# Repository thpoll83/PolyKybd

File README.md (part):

# PolyKybd Split72

Official hardware repository of the PolyKybd Split72 keyboard. If you are looking for the kit, jump immediately to https://www.crowdsupply.com/polykybd/polykybd for registration.

The instructions here are still in a very early stage. There is also a build video available: https://www.youtube.com/watch?v=K5RpbYzx7gw

You can find the matching QMK firmware here: [https://github.com/thpoll83/qmk_firmware/tree/PolyKybd](https://github.com/thpoll83/qmk_firmware/tree/PolyKybd)

## Cloning this repository

This repo is big — around 800 MB of history. Most of that is the board files themselves: the
decorative silkscreen artwork is stored as vector polygons, which makes a single `.kicad_pcb`
around 50 MB, and there are several design generations in the history.

If you just want the current files, use a partial clone. Git then downloads file contents only
when you actually touch them, so a fresh checkout takes seconds instead of many minutes:

```
git clone --filter=blob:none https://github.com/thpoll83/PolyKybd.git
```

The full history is still there and everything works normally — `git log`, `git checkout`, opening
the boards in KiCad. Older revisions of large files are simply fetched on demand. If you want a
plain full clone instead, just leave the `--filter` off.

The PCB projects are the following (**KiCad 9** — the schematics were migrated to the version 9
file format, so KiCad 8 and earlier can no longer open them):

[poly_kybd/poly_kybd_split72_right.kicad_pro](poly_kybd/poly_kybd_split72_right.kicad_pro)
[poly_kybd/poly_kybd_split72_left.kicad_pro](poly_kybd/poly_kybd_split72_left.kicad_pro)

(please just use the projects linked above and ignore any older/backup projects in the folder)

Here are the corresponding schematics for reference (left and right):

You can inspect all individual schematic sheets (with descriptions) here: [Schematic sheets](schematics.md).

The keyboard plates are also KiCad projects, still in an older file format but they open fine in
KiCad 9 (I used 1.2mm aluminum PCBs):

[poly_kybd/poly_kybd_split72_plate_right.kicad_pro](poly_kybd/poly_kybd_split72_plate_right.kicad_pro)
[poly_kybd/poly_kybd_split72_plate_left.kicad_pro](poly_kybd/poly_kybd_split72_plate_left.kicad_pro)

## How to Build

I recommend waiting for the kit that contains all parts and the assembled PCBs. Here a little preview, how that looks like:

The kits are not yet ready, but you can sign up here and get notified as soon as these are available: [https://www.crowdsupply.com/polykybd/polykybd](https://www.crowdsupply.com/polykybd/polykybd)

At the moment, please consider these instructions as experimental. If you want to go ahead with the full experience and build everything from scratch right now: Give it a try and let me know how it worked out!

Independent of your choice, here are the parts you need before putting everything together:

### Prepare Required Parts

* Case (left/right) - You can either 3D print or get them CNCed (but then you should add some threads to the screw holes):
  [parts/export/case/case_polykybd_split72_left_r7.stl](parts/export/case/case_polykybd_split72_left_r7.stl)
  
  [parts/export/case/case_polykybd_split72_right_r7.stl](parts/export/case/case_polykybd_split72_right_r7.stl)
  
  In case the resin print has some deformations, it is best to use a hairdryer to slightly heat the case up and then put something heavy on the bottom to make it flat - it really works.
* Spacer to keep the right distance between plate and PCB (again, can be 3D printed):
  [parts/export/case/spacer.stl](parts/export/case/spacer.stl). If you fit the LED diffuser frame, print [parts/export/case/spacer_diffuser_frame.stl](parts/export/case/spacer_diffuser_frame.stl) instead. It is notched for the frame on both faces, so one part works on either half.
  
* Assembled 4 layers PCB 1.6mm (left/right)
  The latest gerber files with BOM and pick/place file can be found in [poly_kybd/Gerber](poly_kybd/Gerber) I made some final adjusts on the latest version, which I did not yet order (I will let you know as soon as I did).
  [poly_kybd/Gerber/PCB/left-side-v3.2/PolyKybd_Split72_L_3.2.zip](poly_kybd/Gerber/PCB/left-side-v3.2/PolyKybd_Split72_L_3.2.zip)
  [poly_kybd/Gerber/PCB/right-side-v3.2/PolyKybd_Split72_R_3.2.zip](poly_kybd/Gerber/PCB/right-side-v3.2/PolyKybd_Split72_R_3.2.zip)

  My recommendation is to let assemble the PCBs as there are a lot of parts with tiny footprints like the RP2040, the 72 FPC sockets and some more...
  If your PCB fab has an option to verify the parts orientation, please make use of it. I did that as well and never bothered correcting them (since the 'upright' orientation of the part from KiCad and your PCB fab might differ).

  ###### Note:

  In case you make modifications to the PCB in KiCad and export everything you might need to change the hot swap sockets side to the back. The hot swap socket in KiCad is part of the key switch and for some reason I couldn't yet convince KiCad that the manufacturing side is the back...
* Aluminum plates (left/right =) - Can be ordered from PCB manufactures as a 1.2mm aluminum PCB
  [poly_kybd/Gerber/Plate/gerber-left-side-v3-17.11.2023.zip](poly_kybd/Gerber/Plate/gerber-left-side-v3-17.11.2023.zip)
  [poly_kybd/Gerber/Plate/gerber-right-side-v3-17.11.2023.zip](poly_kybd/Gerber/Plate/gerber-right-side-v3-17.11.2023.zip)
* Displays

  - 72 pieces 0.42 inch displays

    - Either you take the 0.42 inch displays from the kit which has the matching length and pin number (maybe I can make them available as single parts as well - see picture above, on the left).
    - Or make them yourself the manual way, by extending a compatible 0.42 inch OLED with a short FPC cable and soldering the two together. See [Making the displays manually](making_the_displays_manually.md) for suppliers and the full soldering instructions.
  - (Optional) 2 pieces 0.96 inch status displays (FPW096W001Z0) or pin compatible (see below), the flex cable length should be about 40mm or you extend it on your own. You can contact this supplier: [FET](https://fetoled.en.alibaba.com/search/product), they have these displays even they are not listed in their online catalogue.

    | PIN   | SIGNAL    | PIN   | SIGNAL |
    | ----- | --------- | ----- | ------ |
    | 1,30  | N/C (GND) | 14    | RES#   |
    | 2,3   | C2P,C2N   | 15    | D/C#   |
    | 4,5   | C1P,C1N   | 16    | R/W#   |
    | 6     | VDDB/VBAT | 17    | E/RD#  |
    | 7     | N/C       | 18~25 | D0~D7  |
    | 8     | VSS       | 26    | IREF   |
    | 9     | VDD       | 27    | VCOMH  |
    | 10~12 | BS0~BS2   | 28    | VCC    |
    | 13    | CS#       | 29    | VLSS   |

    If you don't need the status displays, you can close the display cut-out with the dummy holder: [Dummy Display Holder](parts/export/display_holder/display_holder_dummy_r1.stl)

* MX Compatible key switches (3 or 5 pins) - 72 pieces. From my blog post ( [https://ko-fi.com/post/More-Key-Switch-Testing-While-Waiting-For-The-Asse-B0B8HX1HW](https://ko-fi.com/post/More-Key-Switch-Testing-While-Waiting-For-The-Asse-B0B8HX1HW) ), you can find out, that there are 2 categories of compatible key switches. The ones that work out of the box and the ones that need a little modification. Basically all switches that have an LED slit that is at least 7.5mm wide work. I tested quite some switches and here is the list of tested switches that will work for sure without modification:

  | SWITCH                            | TYPE            | MISC  |
  | --------------------------------- | --------------- | ----- |
  | Aflion Tropical Waters            | Linear          | 68g   |
  | Ashkeebs Alexandrite              | Linear          | 58g   |
  | Blue Dusk Panda                   | Linear          | 62g   |
  | BSUN x Unikeys Udon               | Linear          | 48g   |
  | CK x Haimu Pastel Lemon           | Linear          | 63.5g |
  | Ck x Haimu Pastel Thistle         | Tactile         | 63.5g |
  | Gateron KS-9 (Pro) Blue           | Clicky          | 60g   |
  | Gateron KS-9 (Pro) Brown          | Tactile         | 55g   |
  | Gateron KS-9 (Pro) Green          | Clicky          | 80g   |
  | Gateron KS-9 (Pro) Red            | Linear          | 45g   |
  | Gateron KS-9 (Pro) Yellow         | Linear          | 50g   |
  | Geon Black                        | Tactile         | 60g   |
  | Geon Clear                        | Linear          | 60g   |
  | Geon Yellow                       | Linear          | 63.5g |
  | Glorious Panda                    | Tactile         | 67g   |
  | GOJU Works x Tecsee Safety Switch | Linear          | 65g   |
  | HMX Cthulhu                       | Linear          | 45-50g|
  | HMX Emo                           | Linear          | 40g   |
  | HMX Hazelnut V2                   | Linear          | 43g   |
  | HMX K01 Light                     | Tactile         | 45g   |
  | HMX Lotus                         | Linear          | 62.5g |
  | HMX Su Color Pink                 | Linear          | 45g   |
  | HMX x Sillyworks Sonja            | Linear          | 45g   |
  | HMX x Unikeys Purple Dawn         | Linear          | 55g   |
  | Kailh Novel Keys Cream Switch     | Linear          | 55g   |
  | Kailh Purple Potato               | Tactile         | 63.5g |
  | Kailh x Domikey Knight Saber      | Tactile         | 42g   |
  | Keygeek M3                        | Linear          | 48g   |
  | LCET Grace                        | Linear          | 50g   |
  | LCET Joker                        | Tactile         | 58g   |
  | LCET Pink Queen                   | Tactile         | 58g   |
  | LCET Sprout                       | Linear          | 50g   |
  | MMD Holy Panda V3                 | Tactile         | 45g   |
  | Outemu (Dustproof) Black          | Linear          | 65g   |
  | Outemu (Dustproof) Blue           | Clicky          | 65g   |
  | Outemu (Dustproof) Brown          | Tactile         | 50g   |
  | Outemu (Dustproof) Red            | Linear          | 46g   |
  | Outemu Crystal Clear              | Linear          | 45g   |
  | Outemu Dust-proof Silver          | Linear          | 45g   |
  | Outemu Lemon                      | Silent Tactile  | 35g   |
  | Outemu Panda                      | Tactile         | 50g   |
  | Outemu Peach                      | Linear          | 40g   |
  | Outemu Purple                     | Tactile         | 45g   |
  | Outemu Ocean                      | Linear          | 35g   |
  | Outemu Teal                       | Clicky          | 70g   |
  | Owlab Neon                        | Linear          | 62g   |
  | Tecsee Medium (low profile)       | Linear & Tactile| 50g   |

  Be aware that there are different batches of Gateron KS-9 (with and without 'Pro') switches. Despite the exact same name, they might need the following surgery (better ask before buy).
  So, some switches have an LED slit, but with a little plastic bar in the middle:

  You can simply cut it away with a knife:

  It is not a big deal, just consider it. Here is a list of switches that I successfully tested after this little modification:

  | SWITCH                           | TYPE           | MISC |
  | -------------------------------- | -------------- | ---- |
  | Gateron KS-9 (Pro 2.0) Red       | Linear         | 45g  |
  | Gateron KS-9 (Pro 2.0) White     | Linear         | 35g  |
  | Geon HG [Haimu x Geon] Black     | Linear         | 65g  |
  | Geon HG [Haimu x Geon] White     | Tactile        | 65g  |
  | Geon HG [Haimu x Geon] Red       | Silent Linear  | 65g  |
  | Geon HG [Haimu x Geon] Yellow    | Silent Tactile | 65g  |
  | Kailh BOX V2 Red Switch          | Linear         | 40g  |
  | Kailh Box Cream                  | Linear         | 45g  |
  | Kailh Pro Purple                 | Tactile        | 50g  |
  | Kailh Pro Burgundy               | Linear         | 50g  |
  | Kailh Pro Light Green            | Clicky         | 50g  |
  | Kailh Pro Plum                   | Tactile        | 70g  |
  | Kailh Speed Gold                 | Clicky         | 50g  |
  | Kailh Speed Silver               | Linear         | 50g  |
  | Kailh Speed Bronze               | Clicky         | 50g  |
  | Kailh Speed Copper               | Tactile        | 40g  |
  | Kailh Speed Burnt Orange         | Linear/Tactile | 70g  |
  | Kailh Speed Pro Heavy Army Green | Clicky         | 70g  |
  | Kailh Speed Pro Heavy Yellow     | Linear         | 70g  |
  | Kailh Black                      | Linear         | 60g  |
  | Kailh RGB Red                    | Linear         | 45g  |
  | Kailh RGB Black                  | Linear         | 60g  |
  | Kailh RGB Blue                   | Clicky         | 50g  |
  | Kailh RGB Brown                  | Tactile        | 50g  |

  There are many more switches that will work as long as they have a 7.5mm wide LED slit. Let me know in case you successfully tried another switch, then I can update the list.

* Key Stems - 72 pieces, can be 3D printed (I highly recommend using an SLA printer). There are 3 different profiles available here. You can also modify the source file an make your own profile. If you take the STLs, make sure to always grab the latest version.

  Every plate is in [parts/export/keycap_stem/](parts/export/keycap_stem), named
  `keycap_stem_revAlpha_<width>_<profile>_10p.stl` — where *width* is `1U` or
  **`1U25`** (not `1.25U`) and *profile* is one of `R1`–`R5`, `S1`, `S`, `S5`, e.g.
  `keycap_stem_revAlpha_1U25_R1_10p.stl`. Ten pieces per plate, so divide the
  counts below by ten (rounding up) to know how many of each to print.

  Every piece carries its **profile and revision engraved on the top face**
  (`R5 α`, `S1 α`, …), matching the profile token in the filename — so a printed
  stem can always be traced back to the plate that made it, and a mixed handful
  can be sorted back out.

  - Flat 
    One stem for every row: the `R3` plates (14 pieces 1.25U and 58 pieces 1U).
  - Stepped 
    Rows tilted rather than curved. This works best if the keyboard is inclined by 5 degrees or more, and comes in two variations:
    - *sculpted* (pictured) — `S1` on the front row, `S5` on the back row, `S` on the three rows between: 4x 1.25U S1, 10x 1U S1, 8x 1.25U S, 36x 1U S, 2x 1.25U S5, 12x 1U S5.
    - *uniform* 
      just the `S` plates everywhere (14 pieces 1.25U and 58 pieces 1U) — a flatter feel that is simpler to print, since it is a single plate design.
  - Curved 
    Here you will need `R1` to `R5`: 4x 1.25U R1, 10x 1U R1, 4x 1.25U R2, 12x 1U R2, 2x 1.25U R3, 12x 1U R3, 2x 1.25U R4, 12x 1U R4, 2x 1.25U R5, 12x 1U R5.

  To change a profile or add your own, edit the shared
  [parts/keycap_stem/keycap_stem.scad](parts/keycap_stem/keycap_stem.scad) or add a
  file to [parts/keycap_stem/variants/](parts/keycap_stem/variants), then run
  `parts/keycap_stem/build_stems.sh` — see [parts/README.md](parts/README.md).
* Status display holder (or cover/dummy in case no status display is used), can be 3D printed.
  [parts/export/display_holder/display_holder_r1.stl](parts/export/display_holder/display_holder_r1.stl) / [parts/export/display_holder/display_holder_dummy_r1.stl](parts/export/display_holder/display_holder_dummy_r1.stl)
* LED diffuser frame (optional, recommended) - one part per half. Each key's LED shines through a half-round hole in the plate, and without a diffuser it shows as a bright point. The frame holds all 36 diffusers of one half at their plate positions, connected by a web under the plate. Print it in resin (SLA): it is thin, and the web is close to the 0.8mm minimum wall a print service accepts.
  [parts/export/diffuser/diffuser_frame_left.stl](parts/export/diffuser/diffuser_frame_left.stl) / [parts/export/diffuser/diffuser_frame_right.stl](parts/export/diffuser/diffuser_frame_right.stl) (the `_4x` files stack four copies on top of each other, joined by a sprue so that a print service counts one part; the slicer still needs supports between the copies, and you cut the pins off before fitting)
  With the frame you need the other spacer, `spacer_diffuser_frame.stl` (see Spacer above), because the plain spacer has no room for the web.
* Transparent keycap covers - 72 pieces (from relegendable keycaps [like these](https://de.aliexpress.com/item/1005002996832179.html?spm=a2g0o.order_list.order_list_main.111.49985c5f1EyPsm&gatewayAdapt=glo2deu)), 58x 1U and 14x 1.25U. Various sources sell them on Alibaba, AliExpress, Amazon & Co.
* Optional rotary encoder ([EVQWGD001](https://de.aliexpress.com/i/32990950196.html?gatewayAdapt=gloMsite2deuPcglo2deu) or [Alps EC11 Encoder](https://www.mouser.at/c/electromechanical/encoders/?m=Alps%20Alpine&series=EC11)), [pimoroni trackball](https://mou.sr/3rmFiAO) or [23mm cirque trackpad](https://www.mouser.at/ProductDetail/Cirque/TM023023-2024-002?qs=wd5RIQLrsJhgKZTW4CXgsA%3D%3D&countryCode=DE&currencyCode=EUR) (and a 12 pin FPC cable with pins on the same side, about 50mm to 70mm). For the trackpad you will need another 3D printed holder, either a high one or a low one: 
  [parts/export/cirque_insert/cirque23_slim_insert_r8.stl](parts/export/cirque_insert/cirque23_slim_insert_r8.stl)
  [parts/export/cirque_insert/cirque23_insert_high_r1.stl](parts/export/cirque_insert/cirque23_insert_high_r1.stl)
  If you are not happy with the existing STLs, you can also modify the source file [parts/cirque_insert/cirque23_insert.scad](parts/cirque_insert/cirque23_insert.scad) or [parts/cirque_insert/cirque23_slim_insert.scad](parts/cirque_insert/cirque23_slim_insert.scad). There is also an experimental version for the 35mm cirque track pad: [parts/cirque_insert/cirque35_insert.scad](parts/cirque_insert/cirque35_insert.scad).
* Optional ambient-light + proximity sensor (**highly recommended**) - a [Pimoroni LTR-559 Light & Proximity Sensor breakout](https://shop.pimoroni.com/products/ltr-559-light-proximity-sensor-breakout) plus a matching 5-pin 2.54mm pin header. The Split72 PCB has a dedicated header footprint for it (labelled `3-6V / SDA / SCL / INT / GND`), sharing the Cirque I2C bus - no extra wiring. With the sensor fitted, the firmware automatically drives keycap brightness from the measured light level and wakes the displays when your hand approaches. It is entirely optional (the firmware is a clean no-op when no sensor is present) and side-agnostic (works on whichever half you solder it to). **You must fit it as the very first assembly step** - see the note in [Put Everything Together](#put-everything-together) below, because it does *not* fit through the plate hole and cannot be added later without an almost complete disassembly. 
  ***Note:*** each half has a **single** expansion slot that takes exactly **one** of these optional add-ons - a rotary encoder, a pointing device (trackball/trackpad), *or* the light sensor. So on a given half the sensor is mutually exclusive with the encoder and the pointing device: fitting the sensor means that half has no encoder/trackpad. (You can still put the sensor on one half and a pointing device or encoder on the other.)
* Short USB-C to USB-C cable to connect the two sides (maybe around 50cm).
* USB-C to USB-A/USB-C to connect to your computer.
  ***Note:*** I had a USB-C to USB-A cable and was sitting in front of a laptop with only USB-C ports. Without a USB-C to USB-C cable at hand, I used an USB-A to USB-C adapter. It turned out this USB-C to USB-A cable + USB-A to USB-C adapter construction was only working then the adapter was connected to the laptop. - better use a USB-C to USB-C right away.
* 8 M3x10 hex screws with rounded heads and for the current case version (r4 and later, e.g. r7), you also need 8 M3 hex nuts.

### Put Everything Together

Here is my recommended order:

0. **(Optional but highly recommended) Solder the LTR-559 light + proximity sensor - do this FIRST!**
   ⚠️ The sensor board does **not** fit through the hole in the aluminum plate, so it has to be soldered on **before** the plate goes on. If you add it later you will have to almost completely disassemble the keyboard again. So if there is any chance you want it, fit it now - it is optional in firmware and costs you nothing if you later decide not to use it.
   ⚠️ Each half has a **single** expansion slot shared by the sensor, the rotary encoder and a pointing device (trackball/trackpad) - only **one** of the three fits per half. So fitting the sensor means no encoder or trackpad on that half (you can still fit one of those on the other half). Decide before you start soldering.

   The Split72 PCB has a labelled 5-pin footprint for the sensor (`3-6V / SDA / SCL / INT / GND`). Solder the sensor exactly like this:
   1. Solder the 5-pin header into the PCB footprint.
   2. The plastic spacer strip of the header now has to come off - it holds the sensor board too high to clear the plate. I simply pushed it all the way down/off the pins:
      
   3. It is still too thick, so instead of the plastic spacer use a piece of paper folded twice (roughly 1-2mm) as a temporary shim to set the sensor at a nice low height while you solder the board onto the header pins:
      
   4. After soldering, pull the paper back out. The sensor now sits low and flat, just above the PCB:
      
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
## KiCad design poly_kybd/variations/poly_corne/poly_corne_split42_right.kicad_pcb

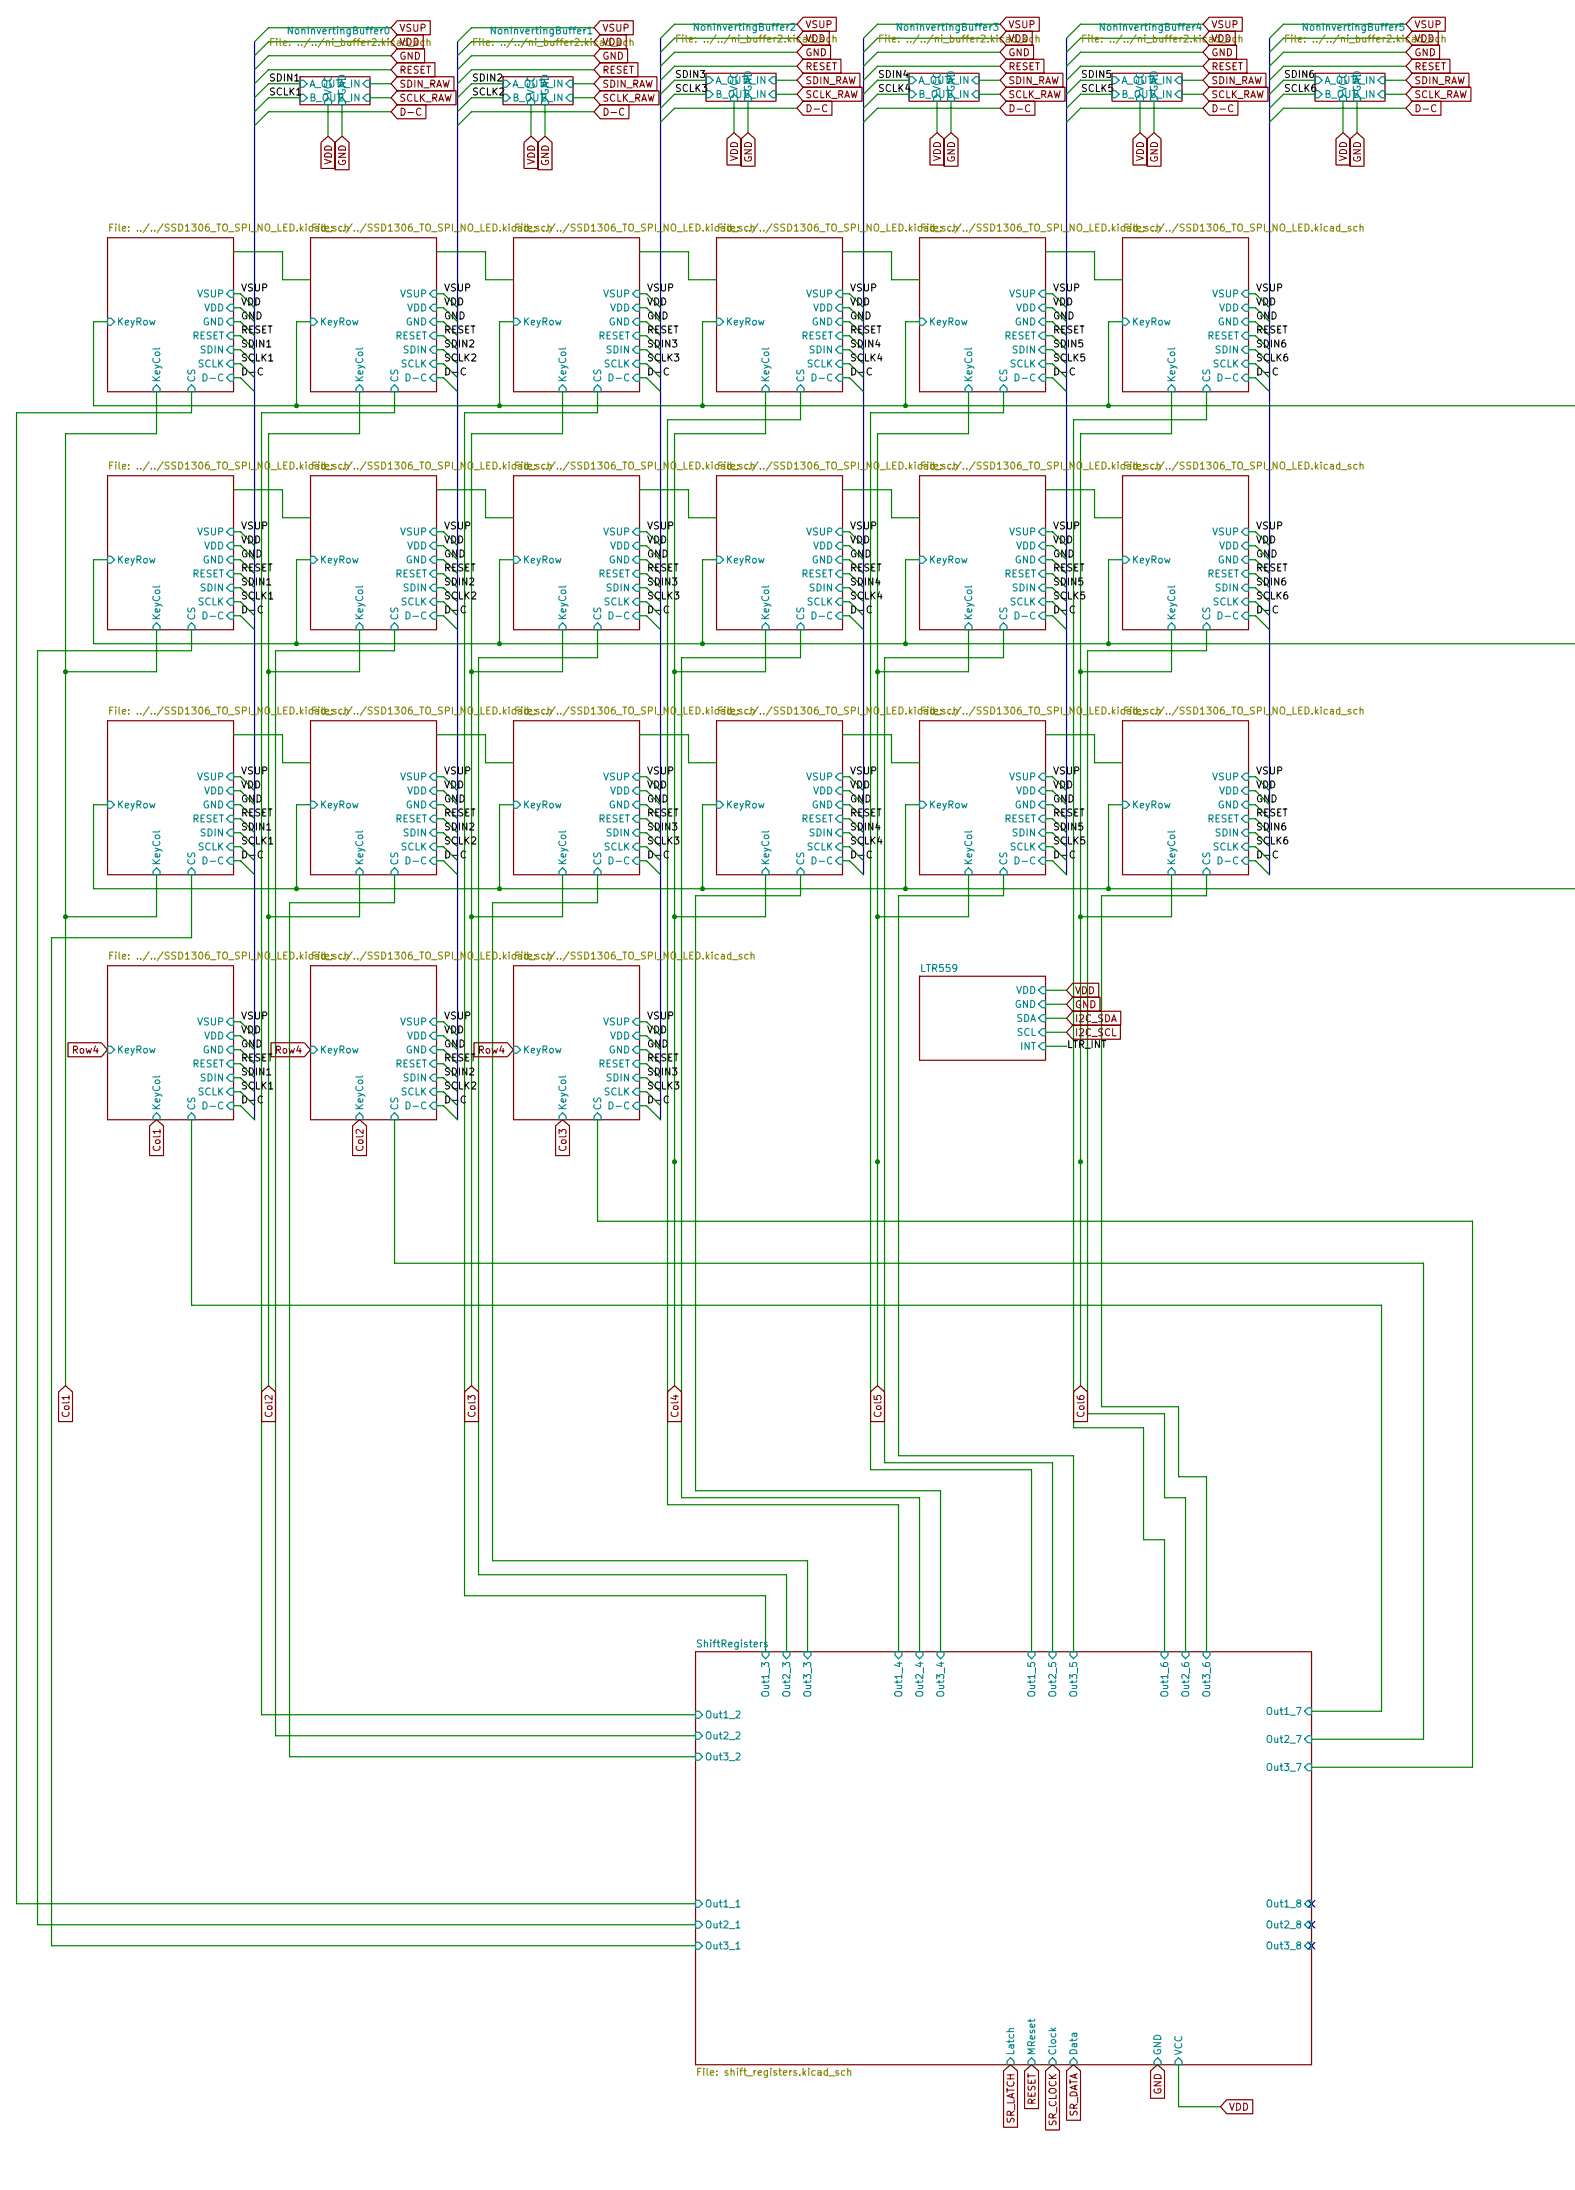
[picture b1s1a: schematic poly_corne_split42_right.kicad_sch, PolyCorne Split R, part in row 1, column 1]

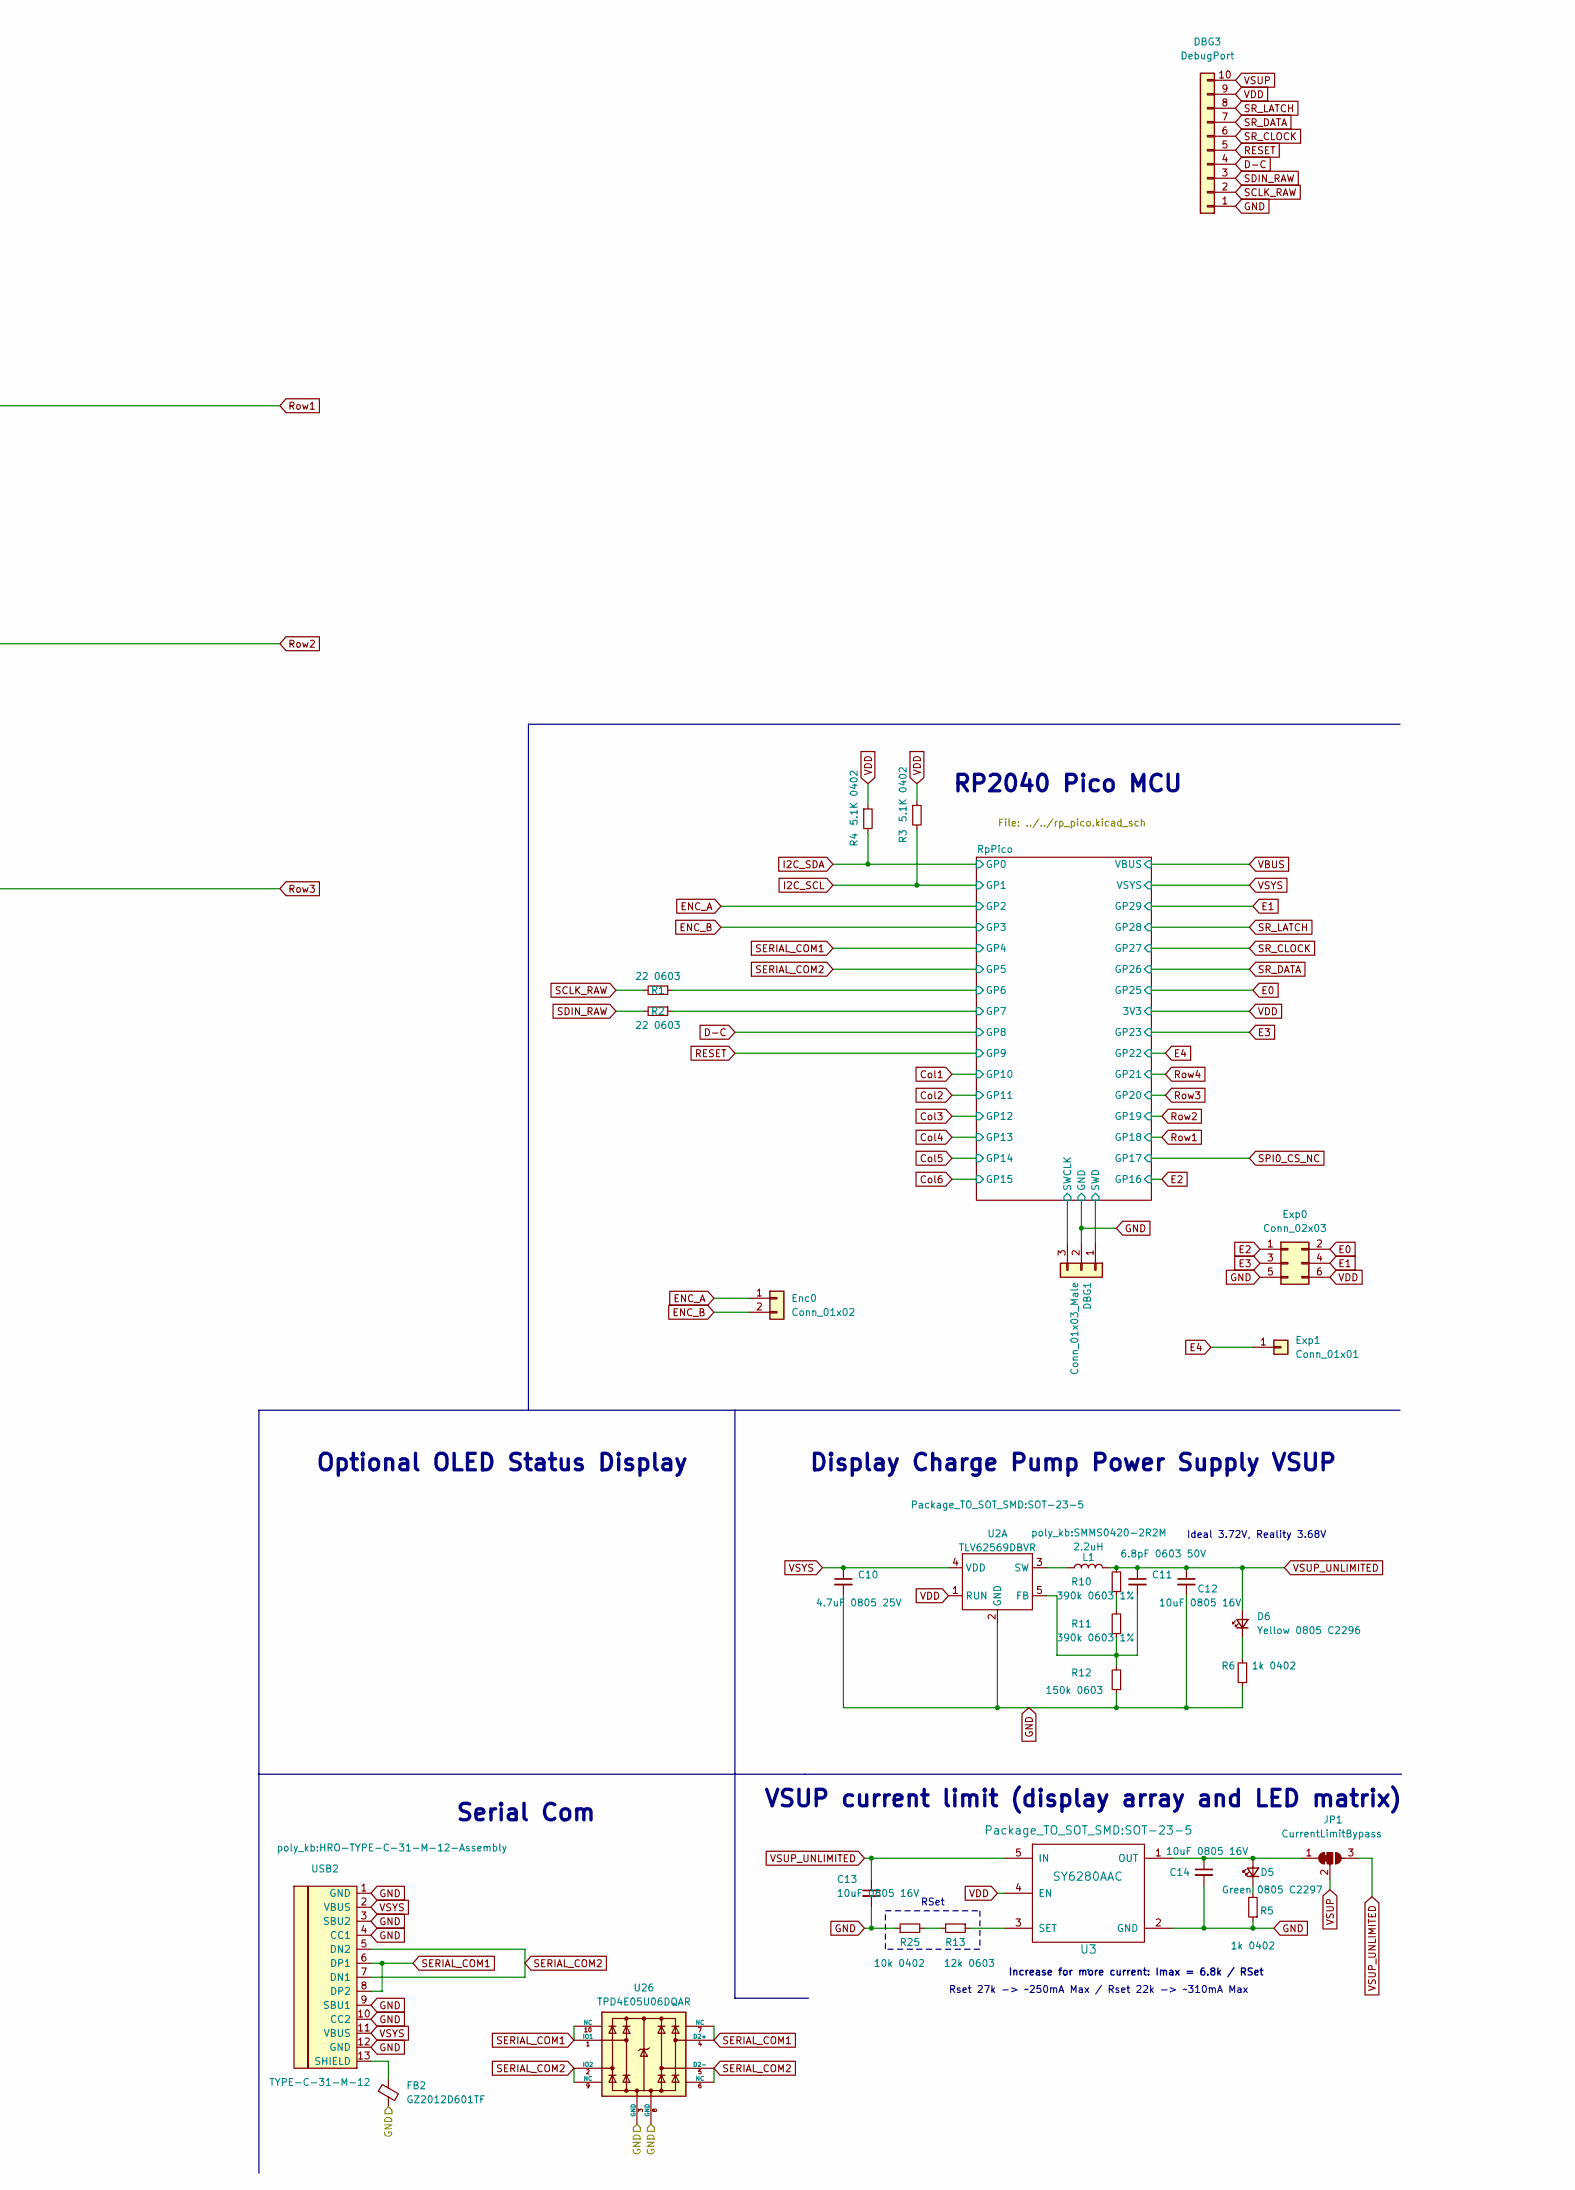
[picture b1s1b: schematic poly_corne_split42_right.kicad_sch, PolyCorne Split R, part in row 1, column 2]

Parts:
C10: 4.7uF 0805 25V; C_0805_2012Metric; MPN C1779; JLC C1779
C11: 6.8pF 0603 50V; C_0603_1608Metric; MPN CL10C6R8CB8NNNC; JLC C318672
C12, C13, C14: 10uF 0805 16V; C_0805_2012Metric; MPN C15850; JLC C15850
D5: Green 0805 C2297; LED_0805_2012Metric; MPN C2297; JLC C2297
D6: Yellow 0805 C2296; LED_0805_2012Metric; MPN C2296; JLC C2296
DBG1: Conn_01x03_Male; PinHeader_1x03_P2.54mm_Vertical; MPN DNP; JLC DNP
DBG3: DebugPort; PinHeader_1x10_P2.54mm_Vertical; MPN DNP; JLC DNP
Enc0: Conn_01x02; PinHeader_1x02_P2.54mm_Vertical; Part Number 1-0201FBV0T
Exp0: Conn_02x03; PinHeader_2x03_P1.27mm_Vertical; Part Number LL1009-2A, 2.54MM 2*3PIN HEADER,LENGTH=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
Exp1: Conn_01x01; PinHeader_1x01_P2.54mm_Vertical
FB2: GZ2012D601TF; L_0805_2012Metric; MPN C1017; JLC C1017
JP1: CurrentLimitBypass; SolderJumper-3_P1.3mm_Bridged12_RoundedPad1.0x1.5mm; MPN DNP; JLC DNP
L1: 2.2uH; SMMS0420-2R2M; MPN C133191; JLC C133191
R1, R2: 22 0603; R_0603_1608Metric; MPN C108405; JLC C108405
R3, R4: 5.1K 0402; R_0402_1005Metric; MPN C144745; JLC C144745
R5, R6: 1k 0402; R_0402_1005Metric; MPN CRCW04021K00FKED; JLC C71623
R10, R11: 390k 0603 1%; R_0603_1608Metric; MPN C137735; JLC C137735
R12: 150k 0603; R_0603_1608Metric; MPN C114660; JLC C114660
R13: 12k 0603; R_0603_1608Metric; MPN C114659; JLC C114659
R25: 10k 0402; R_0402_1005Metric; MPN C60490; JLC C60490
U2: TLV62569DBVR; SOT-23-5; MPN C141836; JLC C141836
U3: SY6280AAC; SOT-23-5; MPN C55136; JLC C55136
U26: TPD4E05U06DQAR; USON-10; MPN C2836386; JLC C2836386
USB2: TYPE-C-31-M-12; HRO-TYPE-C-31-M-12-Assembly; MPN C165948; JLC C165948

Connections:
/RpPico/GPIO6: R1.1; also elsewhere on the board
/RpPico/GPIO7: R2.1; also elsewhere on the board
/RpPico/SWCLK: DBG1.3; also elsewhere on the board
/RpPico/SWD: DBG1.1; also elsewhere on the board
D-C: DBG3.4; also elsewhere on the board
E0: Exp0.2 (+12V); also elsewhere on the board
E1: Exp0.4 (GND); also elsewhere on the board
E2: Exp0.1 (+12V); also elsewhere on the board
E3: Exp0.3 (GND); also elsewhere on the board
E4: Exp1.1; also elsewhere on the board
ENC_A: Enc0.1; also elsewhere on the board
ENC_B: Enc0.2; also elsewhere on the board
GND: C10.2, C12.2, C13.2, C14.2, DBG1.2, DBG3.1, Exp0.5 (GND), FB2.2, R5.1, R6.1, R12.1, R25.1, U2.2 (GND), U3.2 (GND), U26.3 (GND), U26.8 (GND), USB2.1 (GND), USB2.3 (SBU2), USB2.4 (CC1), USB2.9 (SBU1), USB2.10 (CC2), USB2.12 (GND); also elsewhere on the board
I2C_SCL: R3.2; also elsewhere on the board
I2C_SDA: R4.2; also elsewhere on the board
unnamed: C14.1, D5.2 (A), JP1.1 (A), U3.1 (OUT)
unnamed: D5.1 (K), R5.2
unnamed: D6.1 (K), R6.2
unnamed: R10.1, R11.2
unnamed: R13.2, R25.2
unnamed: C11.2, R11.1, R12.2, U2.5 (FB)
unnamed: L1.1, U2.3 (SW)
unnamed: R13.1, U3.3 (SET)
unnamed: FB2.1, USB2.13 (SHIELD)
RESET: DBG3.5; also elsewhere on the board
SCLK_RAW: DBG3.2, R1.2; also elsewhere on the board
SDIN_RAW: DBG3.3, R2.2; also elsewhere on the board
SERIAL_COM1: U26.1 (IO1), U26.4 (D2+), U26.7 (NC), U26.10 (NC), USB2.6 (DP1), USB2.8 (DP2); also elsewhere on the board
SERIAL_COM2: U26.2 (IO2), U26.5 (D2-), U26.6 (NC), U26.9 (NC), USB2.5 (DN2), USB2.7 (DN1); also elsewhere on the board
SR_CLOCK: DBG3.6; also elsewhere on the board
SR_DATA: DBG3.7; also elsewhere on the board
SR_LATCH: DBG3.8; also elsewhere on the board
VDD: DBG3.9, Exp0.6 (GND), R3.1, R4.1, U2.1 (RUN), U3.4 (EN); also elsewhere on the board
VSUP: DBG3.10, JP1.2 (C); also elsewhere on the board
VSUP_UNLIMITED: C11.1, C12.1, C13.1, D6.2 (A), JP1.3 (B), L1.2, R10.2, U3.5 (IN)
VSYS: C10.1, U2.4 (VDD), USB2.2 (VBUS), USB2.11 (VBUS); also elsewhere on the board

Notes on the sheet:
RP2040 Pico MCU
Increase for more current: Imax = 6.8k / RSet
Ideal 3.72V, Reality 3.68V
Optional OLED Status Display
Display Charge Pump Power Supply VSUP
VSUP current limit (display array and LED matrix)
RSet
Serial Com
Rset 27k -> ~250mA Max / Rset 22k -> ~310mA Max

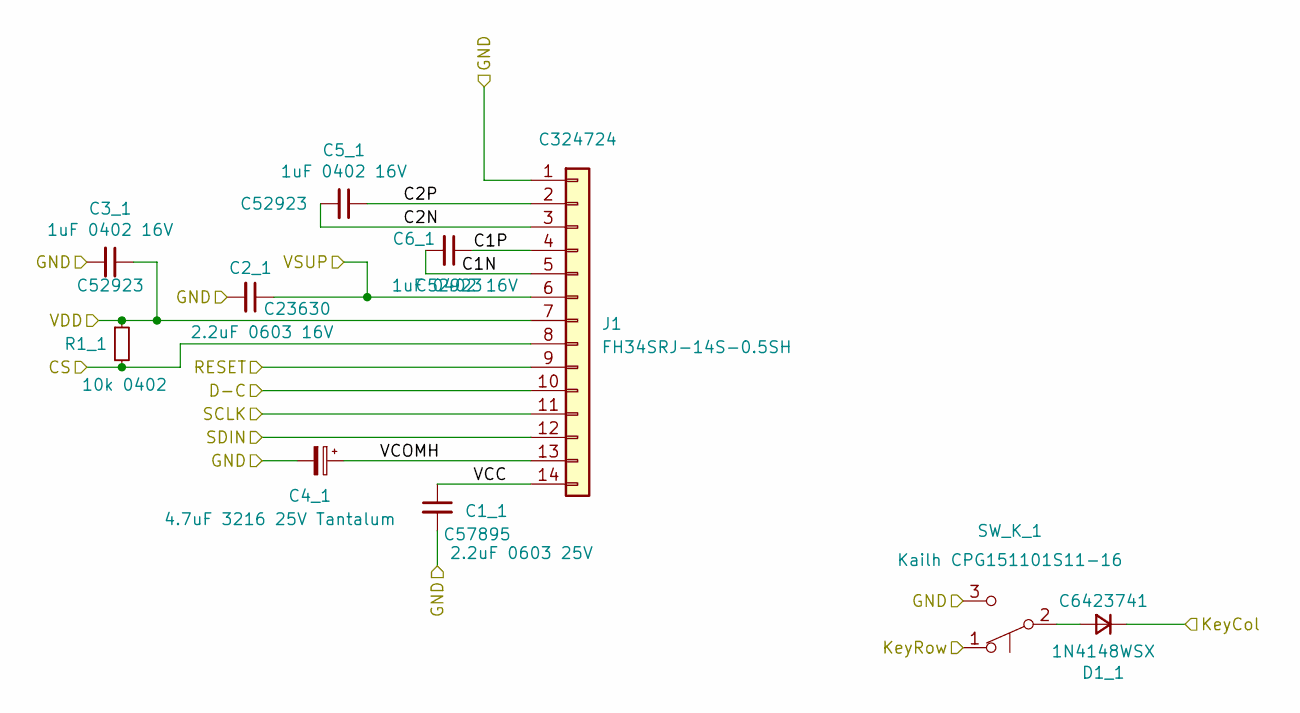
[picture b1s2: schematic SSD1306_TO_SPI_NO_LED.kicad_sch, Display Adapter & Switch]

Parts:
C1_1: 2.2uF 0603 25V; C_0603_1608Metric; MPN C57895; LCSC C57895
C2_1: 2.2uF 0603 16V; C_0603_1608Metric; MPN C23630; LCSC C23630
C3_1, C5_1, C6_1: 1uF 0402 16V; C_0402_1005Metric; MPN C52923; LCSC C52923
C4_1: 4.7uF 3216 25V Tantalum; CP_EIA-3216-18_Kemet-A; MPN 293D475X9025A2TE3; JLC C5380411
D1_1: 1N4148WSX; D_SOD-323Ext; MPN C6423741; LCSC C6423741
J1: FH34SRJ-14S-0.5SH; FH34SRJ14S05SH50-Rev2; MPN C324724; LCSC C324724
R1_1: 10k 0402; R_0402_1005Metric; MPN C60490; LCSC C60490
SW_K_1: Kailh CPG151101S11-16; Kailh_socket_MX_Indicators; MPN C5156480; JLC C5156480

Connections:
/K_L1/C1N: C6_1.2, J1.5
/K_L1/C1P: C6_1.1, J1.4
/K_L1/C2N: C5_1.2, J1.3
/K_L1/C2P: C5_1.1, J1.2
/K_L1/CS: J1.8, R1_1.2; also elsewhere on the board
/K_L1/VCC: C1_1.1, J1.14
/K_L1/VCOMH: C4_1.1, J1.13
/SCLK1: J1.11; also elsewhere on the board
/SDIN1: J1.12; also elsewhere on the board
Col1: D1_1.1 (K); also elsewhere on the board
D-C: J1.10; also elsewhere on the board
GND: C1_1.2, C2_1.2, C3_1.2, C4_1.2, J1.1, SW_K_1.3 (C); also elsewhere on the board
unnamed: D1_1.2 (A), SW_K_1.2 (B)
RESET: J1.9; also elsewhere on the board
Row1: SW_K_1.1 (A); also elsewhere on the board
VDD: C3_1.1, J1.7, R1_1.1; also elsewhere on the board
VSUP: C2_1.1, J1.6; also elsewhere on the board

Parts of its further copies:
C1_2, C1_3, C1_4, C1_5, C1_6, C1_8, C1_9, C1_10, C1_11, C1_12, C1_13, C1_15, C1_16, C1_17, C1_18, C1_19, C1_20, C1_25, C1_26, C1_27: 2.2uF 0603 25V; C_0603_1608Metric; MPN C57895; LCSC C57895
C2_2, C2_3, C2_4, C2_5, C2_6, C2_8, C2_9, C2_10, C2_11, C2_12, C2_13, C2_15, C2_16, C2_17, C2_18, C2_19, C2_20, C2_25, C2_26, C2_27: 2.2uF 0603 16V; C_0603_1608Metric; MPN C23630; LCSC C23630
C3_2, C3_3, C3_4, C3_5, C3_6, C3_8, C3_9, C3_10, C3_11, C3_12, C3_13, C3_15, C3_16, C3_17, C3_18, C3_19, C3_20, C3_25, C3_26, C3_27, C5_2, C5_3, C5_4, C5_5, C5_6, C5_8, C5_9, C5_10, C5_11, C5_12, C5_13, C5_15, C5_16, C5_17, C5_18, C5_19, C5_20, C5_25, C5_26, C5_27, C6_2, C6_3, C6_4, C6_5, C6_6, C6_8, C6_9, C6_10, C6_11, C6_12, C6_13, C6_15, C6_16, C6_17, C6_18, C6_19, C6_20, C6_25, C6_26, C6_27: 1uF 0402 16V; C_0402_1005Metric; MPN C52923; LCSC C52923
C4_2, C4_3, C4_4, C4_5, C4_6, C4_8, C4_9, C4_10, C4_11, C4_12, C4_13, C4_15, C4_16, C4_17, C4_18, C4_19, C4_20, C4_25, C4_26, C4_27: 4.7uF 3216 25V Tantalum; CP_EIA-3216-18_Kemet-A; MPN 293D475X9025A2TE3; JLC C5380411
D1_2, D1_3, D1_4, D1_5, D1_6, D1_8, D1_9, D1_10, D1_11, D1_12, D1_13, D1_15, D1_16, D1_17, D1_18, D1_19, D1_20, D1_25, D1_26, D1_27: 1N4148WSX; D_SOD-323Ext; MPN C6423741; LCSC C6423741
J2, J3, J4, J5, J6, J8, J9, J10, J11, J12, J13, J15, J16, J17, J18, J19, J20, J25, J26, J27: FH34SRJ-14S-0.5SH; FH34SRJ14S05SH50-Rev2; MPN C324724; LCSC C324724
R1_2, R1_3, R1_4, R1_5, R1_6, R1_8, R1_9, R1_10, R1_11, R1_12, R1_13, R1_15, R1_16, R1_17, R1_18, R1_19, R1_20, R1_25, R1_26, R1_27: 10k 0402; R_0402_1005Metric; MPN C60490; LCSC C60490
SW_K_2, SW_K_3, SW_K_4, SW_K_5, SW_K_6, SW_K_7, SW_K_8, SW_K_9, SW_K_10, SW_K_11, SW_K_12, SW_K_13, SW_K_14, SW_K_15, SW_K_16, SW_K_17, SW_K_18, SW_K_19, SW_K_20, SW_K_21: Kailh CPG151101S11-16; Kailh_socket_MX_Indicators; MPN C5156480; JLC C5156480

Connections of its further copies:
/K_1/C1N: C6_2.2, J2.5
/K_1/C1P: C6_2.1, J2.4
/K_1/C2N: C5_2.2, J2.3
/K_1/C2P: C5_2.1, J2.2
/K_1/CS: J2.8, R1_2.2; also elsewhere on the board
/K_1/VCC: C1_2.1, J2.14
/K_1/VCOMH: C4_2.1, J2.13
/K_2/C1N: C6_3.2, J3.5
/K_2/C1P: C6_3.1, J3.4
/K_2/C2N: C5_3.2, J3.3
/K_2/C2P: C5_3.1, J3.2
/K_2/CS: J3.8, R1_3.2; also elsewhere on the board
/K_2/VCC: C1_3.1, J3.14
/K_2/VCOMH: C4_3.1, J3.13
/K_3/C1N: C6_4.2, J4.5
/K_3/C1P: C6_4.1, J4.4
/K_3/C2N: C5_4.2, J4.3
/K_3/C2P: C5_4.1, J4.2
/K_3/CS: J4.8, R1_4.2; also elsewhere on the board
/K_3/VCC: C1_4.1, J4.14
/K_3/VCOMH: C4_4.1, J4.13
/K_4/C1N: C6_5.2, J5.5
/K_4/C1P: C6_5.1, J5.4
/K_4/C2N: C5_5.2, J5.3
/K_4/C2P: C5_5.1, J5.2
/K_4/CS: J5.8, R1_5.2; also elsewhere on the board
/K_4/VCC: C1_5.1, J5.14
/K_4/VCOMH: C4_5.1, J5.13
/K_5/C1N: C6_6.2, J6.5
/K_5/C1P: C6_6.1, J6.4
/K_5/C2N: C5_6.2, J6.3
/K_5/C2P: C5_6.1, J6.2
/K_5/CS: J6.8, R1_6.2; also elsewhere on the board
/K_5/VCC: C1_6.1, J6.14
/K_5/VCOMH: C4_6.1, J6.13
/K_A/C1N: C6_16.2, J16.5
/K_A/C1P: C6_16.1, J16.4
/K_A/C2N: C5_16.2, J16.3
/K_A/C2P: C5_16.1, J16.2
/K_A/CS: J16.8, R1_16.2; also elsewhere on the board
/K_A/VCC: C1_16.1, J16.14
/K_A/VCOMH: C4_16.1, J16.13
/K_B/C1N: C6_27.2, J27.5
/K_B/C1P: C6_27.1, J27.4
/K_B/C2N: C5_27.2, J27.3
/K_B/C2P: C5_27.1, J27.2
/K_B/CS: J27.8, R1_27.2; also elsewhere on the board
/K_B/VCC: C1_27.1, J27.14
/K_B/VCOMH: C4_27.1, J27.13
/K_C/C1N: C6_25.2, J25.5
/K_C/C1P: C6_25.1, J25.4
/K_C/C2N: C5_25.2, J25.3
/K_C/C2P: C5_25.1, J25.2
/K_C/CS: J25.8, R1_25.2; also elsewhere on the board
/K_C/VCC: C1_25.1, J25.14
/K_C/VCOMH: C4_25.1, J25.13
/K_D/C1N: C6_18.2, J18.5
/K_D/C1P: C6_18.1, J18.4
/K_D/C2N: C5_18.2, J18.3
/K_D/C2P: C5_18.1, J18.2
/K_D/CS: J18.8, R1_18.2; also elsewhere on the board
/K_D/VCC: C1_18.1, J18.14
/K_D/VCOMH: C4_18.1, J18.13
/K_E/C1N: C6_11.2, J11.5
/K_E/C1P: C6_11.1, J11.4
/K_E/C2N: C5_11.2, J11.3
/K_E/C2P: C5_11.1, J11.2
/K_E/CS: J11.8, R1_11.2; also elsewhere on the board
/K_E/VCC: C1_11.1, J11.14
/K_E/VCOMH: C4_11.1, J11.13
/K_F/C1N: C6_19.2, J19.5
/K_F/C1P: C6_19.1, J19.4
/K_F/C2N: C5_19.2, J19.3
/K_F/C2P: C5_19.1, J19.2
/K_F/CS: J19.8, R1_19.2; also elsewhere on the board
/K_F/VCC: C1_19.1, J19.14
/K_F/VCOMH: C4_19.1, J19.13
/K_G/C1N: C6_20.2, J20.5
/K_G/C1P: C6_20.1, J20.4
/K_G/C2N: C5_20.2, J20.3
/K_G/C2P: C5_20.1, J20.2
/K_G/CS: J20.8, R1_20.2; also elsewhere on the board
/K_G/VCC: C1_20.1, J20.14
/K_G/VCOMH: C4_20.1, J20.13
/K_L2/C1N: C6_8.2, J8.5
/K_L2/C1P: C6_8.1, J8.4
/K_L2/C2N: C5_8.2, J8.3
/K_L2/C2P: C5_8.1, J8.2
/K_L2/CS: J8.8, R1_8.2; also elsewhere on the board
/K_L2/VCC: C1_8.1, J8.14
/K_L2/VCOMH: C4_8.1, J8.13
/K_L3/C1N: C6_15.2, J15.5
/K_L3/C1P: C6_15.1, J15.4
/K_L3/C2N: C5_15.2, J15.3
/K_L3/C2P: C5_15.1, J15.2
/K_L3/CS: J15.8, R1_15.2; also elsewhere on the board
/K_L3/VCC: C1_15.1, J15.14
/K_L3/VCOMH: C4_15.1, J15.13
/K_Q/C1N: C6_9.2, J9.5
/K_Q/C1P: C6_9.1, J9.4
/K_Q/C2N: C5_9.2, J9.3
/K_Q/C2P: C5_9.1, J9.2
/K_Q/CS: J9.8, R1_9.2; also elsewhere on the board
/K_Q/VCC: C1_9.1, J9.14
/K_Q/VCOMH: C4_9.1, J9.13
/K_R/C1N: C6_12.2, J12.5
/K_R/C1P: C6_12.1, J12.4
/K_R/C2N: C5_12.2, J12.3
/K_R/C2P: C5_12.1, J12.2
/K_R/CS: J12.8, R1_12.2; also elsewhere on the board
/K_R/VCC: C1_12.1, J12.14
/K_R/VCOMH: C4_12.1, J12.13
/K_S/C1N: C6_17.2, J17.5
/K_S/C1P: C6_17.1, J17.4
/K_S/C2N: C5_17.2, J17.3
/K_S/C2P: C5_17.1, J17.2
/K_S/CS: J17.8, R1_17.2; also elsewhere on the board
/K_S/VCC: C1_17.1, J17.14
/K_S/VCOMH: C4_17.1, J17.13
/K_T/C1N: C6_13.2, J13.5
/K_T/C1P: C6_13.1, J13.4
/K_T/C2N: C5_13.2, J13.3
/K_T/C2P: C5_13.1, J13.2
/K_T/CS: J13.8, R1_13.2; also elsewhere on the board
/K_T/VCC: C1_13.1, J13.14
/K_T/VCOMH: C4_13.1, J13.13
/K_V/C1N: C6_26.2, J26.5
/K_V/C1P: C6_26.1, J26.4
/K_V/C2N: C5_26.2, J26.3
/K_V/C2P: C5_26.1, J26.2
/K_V/CS: J26.8, R1_26.2; also elsewhere on the board
/K_V/VCC: C1_26.1, J26.14
/K_V/VCOMH: C4_26.1, J26.13
/K_W/C1N: C6_10.2, J10.5
/K_W/C1P: C6_10.1, J10.4
/K_W/C2N: C5_10.2, J10.3
/K_W/C2P: C5_10.1, J10.2
/K_W/CS: J10.8, R1_10.2; also elsewhere on the board
/K_W/VCC: C1_10.1, J10.14
/K_W/VCOMH: C4_10.1, J10.13
/SCLK1: J8.11, J15.11, J25.11; also elsewhere on the board
/SCLK2: J2.11, J9.11, J16.11, J26.11; also elsewhere on the board
/SCLK3: J3.11, J10.11, J17.11, J27.11; also elsewhere on the board
/SCLK4: J4.11, J11.11, J18.11; also elsewhere on the board
/SCLK5: J5.11, J12.11, J19.11; also elsewhere on the board
/SCLK6: J6.11, J13.11, J20.11; also elsewhere on the board
/SDIN1: J8.12, J15.12, J25.12; also elsewhere on the board
/SDIN2: J2.12, J9.12, J16.12, J26.12; also elsewhere on the board
/SDIN3: J3.12, J10.12, J17.12, J27.12; also elsewhere on the board
/SDIN4: J4.12, J11.12, J18.12; also elsewhere on the board
/SDIN5: J5.12, J12.12, J19.12; also elsewhere on the board
/SDIN6: J6.12, J13.12, J20.12; also elsewhere on the board
Col1: D1_8.1 (K), D1_15.1 (K), D1_25.1 (K); also elsewhere on the board
Col2: D1_2.1 (K), D1_9.1 (K), D1_16.1 (K), D1_26.1 (K); also elsewhere on the board
Col3: D1_3.1 (K), D1_10.1 (K), D1_17.1 (K), D1_27.1 (K); also elsewhere on the board
Col4: D1_4.1 (K), D1_11.1 (K), D1_18.1 (K); also elsewhere on the board
Col5: D1_5.1 (K), D1_12.1 (K), D1_19.1 (K); also elsewhere on the board
Col6: D1_6.1 (K), D1_13.1 (K), D1_20.1 (K); also elsewhere on the board
D-C: J2.10, J3.10, J4.10, J5.10, J6.10, J8.10, J9.10, J10.10, J11.10, J12.10, J13.10, J15.10, J16.10, J17.10, J18.10, J19.10, J20.10, J25.10, J26.10, J27.10; also elsewhere on the board
GND: C1_2.2, C1_3.2, C1_4.2, C1_5.2, C1_6.2, C1_8.2, C1_9.2, C1_10.2, C1_11.2, C1_12.2, C1_13.2, C1_15.2, C1_16.2, C1_17.2, C1_18.2, C1_19.2, C1_20.2, C1_25.2, C1_26.2, C1_27.2, C2_2.2, C2_3.2, C2_4.2, C2_5.2, C2_6.2, C2_8.2, C2_9.2, C2_10.2, C2_11.2, C2_12.2, C2_13.2, C2_15.2, C2_16.2, C2_17.2, C2_18.2, C2_19.2, C2_20.2, C2_25.2, C2_26.2, C2_27.2, C3_2.2, C3_3.2, C3_4.2, C3_5.2, C3_6.2, C3_8.2, C3_9.2, C3_10.2, C3_11.2, C3_12.2, C3_13.2, C3_15.2, C3_16.2, C3_17.2, C3_18.2, C3_19.2, C3_20.2, C3_25.2, C3_26.2, C3_27.2, C4_2.2, C4_3.2, C4_4.2, C4_5.2, C4_6.2, C4_8.2, C4_9.2, C4_10.2, C4_11.2, C4_12.2, C4_13.2, C4_15.2, C4_16.2, C4_17.2, C4_18.2, C4_19.2, C4_20.2, C4_25.2, C4_26.2, C4_27.2, J2.1, J3.1, J4.1, J5.1, J6.1, J8.1, J9.1, J10.1, J11.1, J12.1, J13.1, J15.1, J16.1, J17.1, J18.1, J19.1, J20.1, J25.1, J26.1, J27.1, SW_K_2.3 (C), SW_K_3.3 (C), SW_K_4.3 (C), SW_K_5.3 (C), SW_K_6.3 (C), SW_K_7.3 (C), SW_K_8.3 (C), SW_K_9.3 (C), SW_K_10.3 (C), SW_K_11.3 (C), SW_K_12.3 (C), SW_K_13.3 (C), SW_K_14.3 (C), SW_K_15.3 (C), SW_K_16.3 (C), SW_K_17.3 (C), SW_K_18.3 (C), SW_K_19.3 (C), SW_K_20.3 (C), SW_K_21.3 (C); also elsewhere on the board
unnamed: D1_2.2 (A), SW_K_2.2 (B)
unnamed: D1_3.2 (A), SW_K_3.2 (B)
unnamed: D1_4.2 (A), SW_K_4.2 (B)
unnamed: D1_5.2 (A), SW_K_5.2 (B)
unnamed: D1_6.2 (A), SW_K_6.2 (B)
unnamed: D1_8.2 (A), SW_K_8.2 (B)
unnamed: D1_9.2 (A), SW_K_9.2 (B)
unnamed: D1_10.2 (A), SW_K_10.2 (B)
unnamed: D1_11.2 (A), SW_K_11.2 (B)
unnamed: D1_12.2 (A), SW_K_12.2 (B)
unnamed: D1_13.2 (A), SW_K_13.2 (B)
unnamed: D1_15.2 (A), SW_K_15.2 (B)
unnamed: D1_16.2 (A), SW_K_16.2 (B)
unnamed: D1_17.2 (A), SW_K_17.2 (B)
unnamed: D1_18.2 (A), SW_K_18.2 (B)
unnamed: D1_19.2 (A), SW_K_19.2 (B)
unnamed: D1_20.2 (A), SW_K_20.2 (B)
unnamed: D1_25.2 (A), SW_K_7.2 (B)
unnamed: D1_26.2 (A), SW_K_14.2 (B)
unnamed: D1_27.2 (A), SW_K_21.2 (B)
RESET: J2.9, J3.9, J4.9, J5.9, J6.9, J8.9, J9.9, J10.9, J11.9, J12.9, J13.9, J15.9, J16.9, J17.9, J18.9, J19.9, J20.9, J25.9, J26.9, J27.9; also elsewhere on the board
Row1: SW_K_2.1 (A), SW_K_3.1 (A), SW_K_4.1 (A), SW_K_5.1 (A), SW_K_6.1 (A); also elsewhere on the board
Row2: SW_K_8.1 (A), SW_K_9.1 (A), SW_K_10.1 (A), SW_K_11.1 (A), SW_K_12.1 (A), SW_K_13.1 (A); also elsewhere on the board
Row3: SW_K_15.1 (A), SW_K_16.1 (A), SW_K_17.1 (A), SW_K_18.1 (A), SW_K_19.1 (A), SW_K_20.1 (A); also elsewhere on the board
Row4: SW_K_7.1 (A), SW_K_14.1 (A), SW_K_21.1 (A); also elsewhere on the board
VDD: C3_2.1, C3_3.1, C3_4.1, C3_5.1, C3_6.1, C3_8.1, C3_9.1, C3_10.1, C3_11.1, C3_12.1, C3_13.1, C3_15.1, C3_16.1, C3_17.1, C3_18.1, C3_19.1, C3_20.1, C3_25.1, C3_26.1, C3_27.1, J2.7, J3.7, J4.7, J5.7, J6.7, J8.7, J9.7, J10.7, J11.7, J12.7, J13.7, J15.7, J16.7, J17.7, J18.7, J19.7, J20.7, J25.7, J26.7, J27.7, R1_2.1, R1_3.1, R1_4.1, R1_5.1, R1_6.1, R1_8.1, R1_9.1, R1_10.1, R1_11.1, R1_12.1, R1_13.1, R1_15.1, R1_16.1, R1_17.1, R1_18.1, R1_19.1, R1_20.1, R1_25.1, R1_26.1, R1_27.1; also elsewhere on the board
VSUP: C2_2.1, C2_3.1, C2_4.1, C2_5.1, C2_6.1, C2_8.1, C2_9.1, C2_10.1, C2_11.1, C2_12.1, C2_13.1, C2_15.1, C2_16.1, C2_17.1, C2_18.1, C2_19.1, C2_20.1, C2_25.1, C2_26.1, C2_27.1, J2.6, J3.6, J4.6, J5.6, J6.6, J8.6, J9.6, J10.6, J11.6, J12.6, J13.6, J15.6, J16.6, J17.6, J18.6, J19.6, J20.6, J25.6, J26.6, J27.6; also elsewhere on the board
